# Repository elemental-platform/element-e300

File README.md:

# element-e300
Wireless carbon dioxide sensor based on RFM69 radio

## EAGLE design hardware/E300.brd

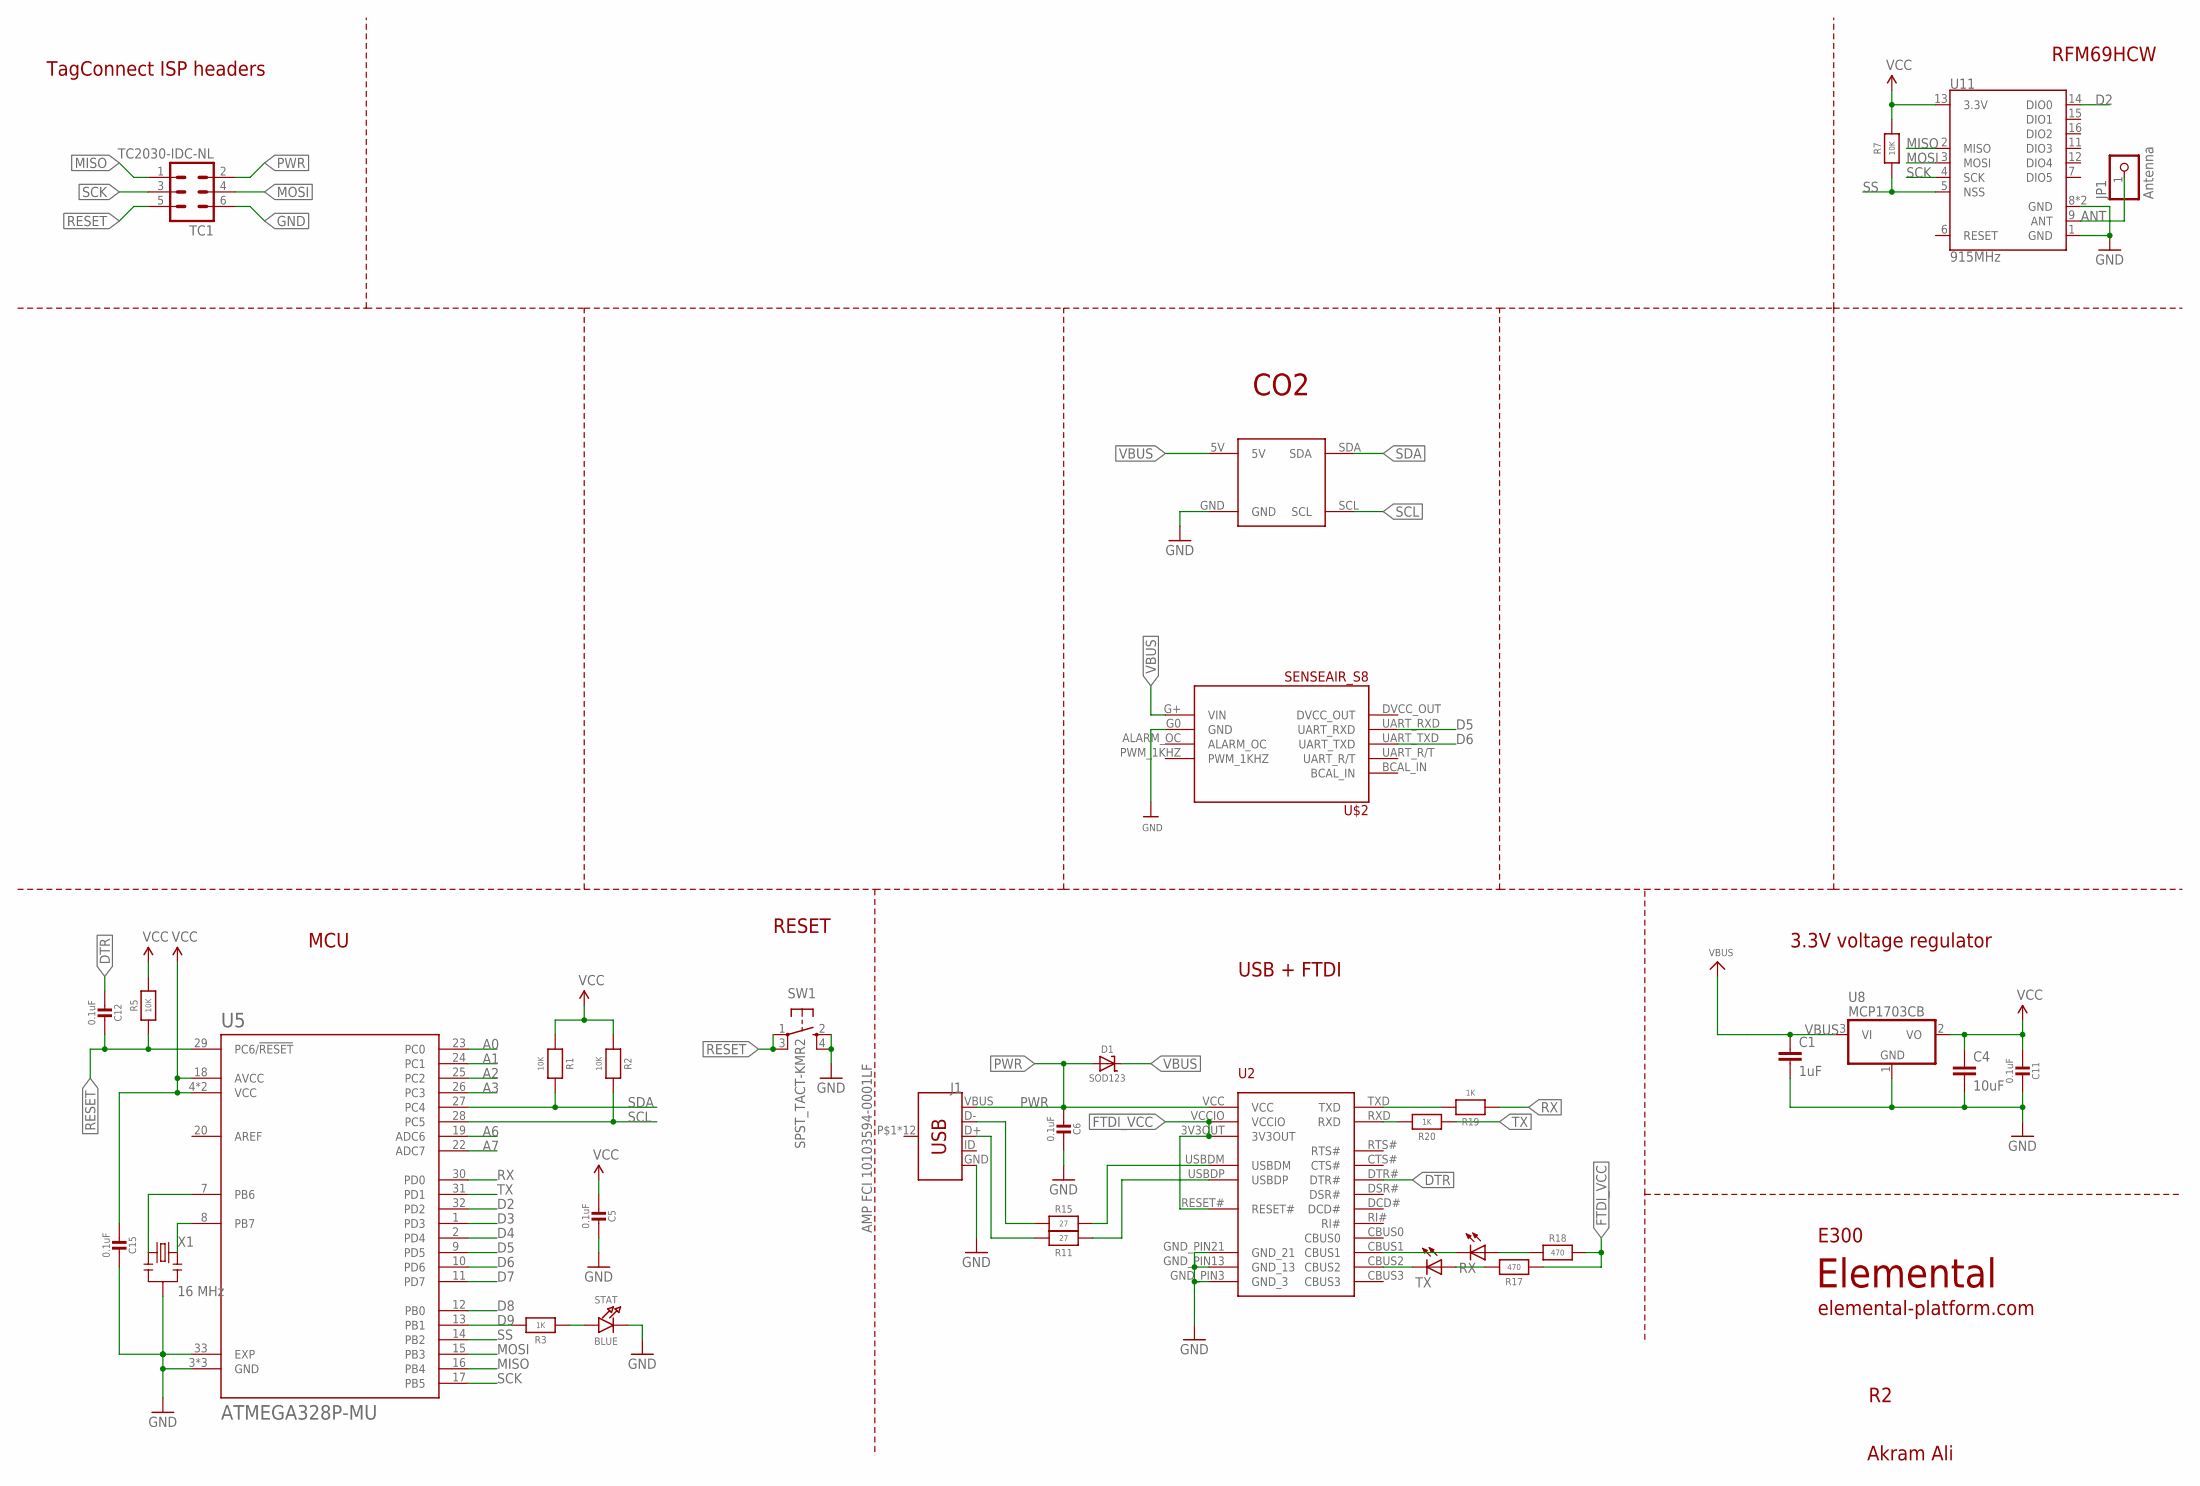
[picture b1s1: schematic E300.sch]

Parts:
C1: 1uF; 0805; MPN CC0805ZRY5V8BB105
C4: 10uF; 0805; MPN CC0805KKX5R6BB106
C5, C6, C11, C12, C15: 0.1uF; MICROBUILDER__0402MP; MPN GRM155R71C104KA88J
D1: SOD123; MICROBUILDER_SOD-123; MPN SD103AW-13-F
J1: AMP FCI 10103594-0001LF; USB-MICROB-PTH
JP1: Antenna; 1X01-CLEANBIG; MPN Helical antenna
R1, R2: 10K; MICROBUILDER__0402MP; MPN RC0402JR-071KL
R3: 1K; MICROBUILDER__0402MP; MPN RC0402JR-0710KL
R5, R7: 10K; MICROBUILDER__0402MP; MPN RC0402JR-0710KL
R11, R15: 27; MICROBUILDER__0402MP; MPN RC0402JR-0727RL
R17, R18: 470; MICROBUILDER__0402MP; MPN RC0402JR-07470RL
R19, R20: 1K; MICROBUILDER__0402MP; MPN RC0402JR-071KL
RX: LEDCHIPLED_0805; CHIPLED_0805; MPN LG R971-KN-1
STAT: BLUE; CHIPLED_0805_NOOUTLINE
SW1: SPST_TACT-KMR2; KMR2
TC1: TC2030-IDC-NL
TX: LEDCHIPLED_0805; CHIPLED_0805; MPN LG R971-KN-1
U2: FT231XQ-R; FTDI_FT231XQ-R_PACKAGE; MPN FT231XQ-R
U5: ATMEGA328P-MU; QFN50P500X500X100-33N; MPN ATMEGA328P-MU
U6: K30-CO2-I2C
U8: MCP1703CB; SOT23; MPN MCP1703T-3302E/CB
U11: 915MHz; RFM69HCW-XXXS2; MPN RFM69HCW
U$2: SENSEAIR_S8
X1: 16 MHz; RESONATOR-SMD; MPN CSTCE16M0V53-R0

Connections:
A0: U5.23 (PC0)
A1: U5.24 (PC1)
A2: U5.25 (PC2)
A3: U5.26 (PC3)
A6: U5.19 (ADC6)
A7: U5.22 (ADC7)
ANT: JP1.1, U11.9 (ANT)
D2: U5.32 (PD2), U11.14 (DIO0)
D3: U5.1 (PD3)
D4: U5.2 (PD4)
D5: U5.9 (PD5), U$2.UART_RXD
D6: U5.10 (PD6), U$2.UART_TXD
D7: U5.11 (PD7)
D8: U5.12 (PB0)
D9: R3.2, U5.13 (PB1)
DTR: C12.2, U2.DTR#
FTDI_VCC: R17.1, R18.2, U2.3V3OUT, U2.RESET#, U2.VCCIO
GND: C1.2, C4.2, C5.1, C6.1, C11.1, C15.1, J1.GND, STAT.C, SW1.2 (S), SW1.4 (S1), TC1.6, U2.GND_PIN3 (GND_3), U2.GND_PIN13 (GND_13), U2.GND_PIN21 (GND_21), U5.3 (GND), U5.5 (GND), U5.21 (GND), U5.33 (EXP), U6.GND, U8.1 (GND), U11.1 (GND), U11.8 (GND), U11.10 (GND), U$2.G0 (GND), X1.2
MISO: TC1.1, U5.16 (PB4), U11.2 (MISO)
MOSI: TC1.4, U5.15 (PB3), U11.3 (MOSI)
unnamed: R20.2, U2.RXD
unnamed: R19.2, U2.TXD
unnamed: U5.8 (PB7), X1.3
unnamed: U5.7 (PB6), X1.1
unnamed: R3.1, STAT.A
unnamed: RX.C, U2.CBUS1
unnamed: TX.C, U2.CBUS2
unnamed: R15.2, U2.USBDM
unnamed: R11.1, U2.USBDP
unnamed: R18.1, RX.A
unnamed: R17.2, TX.A
unnamed: J1.D-, R15.1
unnamed: J1.D+, R11.2
PWR: C6.2, D1.A, J1.VBUS, TC1.2, U2.VCC
RESET: C12.1, R5.1, SW1.1, SW1.3 (P1), TC1.5, U5.29 (PC6/!RESET)
RX: R19.1, U5.30 (PD0)
SCK: TC1.3, U5.17 (PB5), U11.4 (SCK)
SCL: R2.2, U5.28 (PC5), U6.SCL
SDA: R1.2, U5.27 (PC4), U6.SDA
SS: R7.1, U5.14 (PB2), U11.5 (NSS)
TX: R20.1, U5.31 (PD1)
VBUS: C1.1, D1.C, U6.5V, U8.3 (VI), U$2.G+ (VIN)
VCC: C4.1, C5.2, C11.2, C15.2, R1.1, R2.1, R5.2, R7.2, U5.4 (VCC), U5.6 (VCC), U5.18 (AVCC), U8.2 (VO), U11.13 (3.3V)

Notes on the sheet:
TagConnect ISP headers
3.3V voltage regulator
Elemental
E300
Akram Ali
USB + FTDI
elemental-platform.com
RFM69HCW
MCU
RESET
CO2

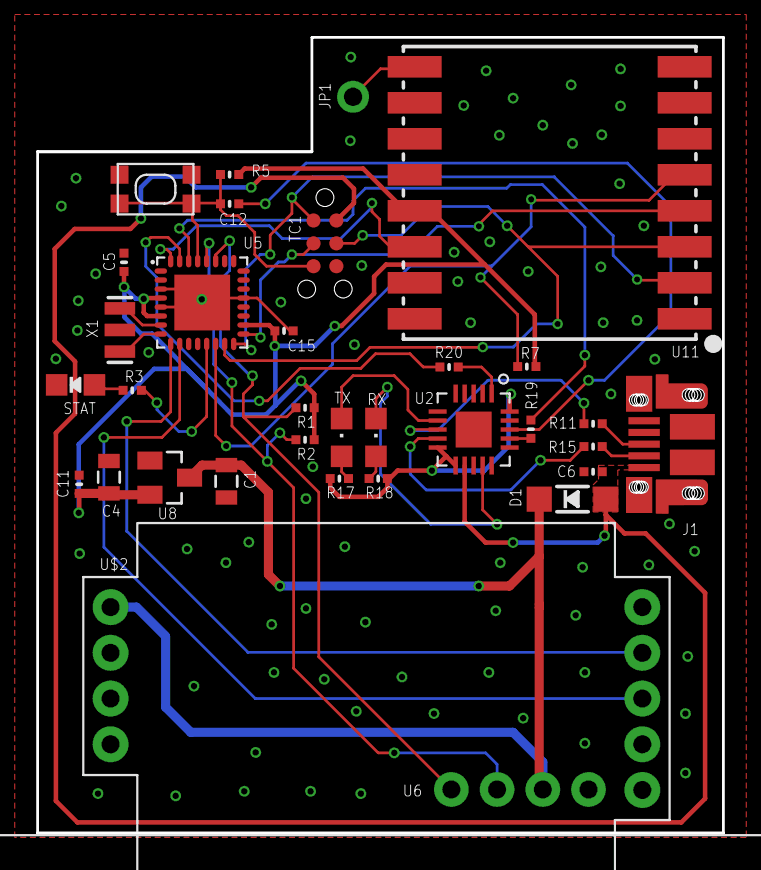
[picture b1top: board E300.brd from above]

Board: 2 copper layers, 38.1 x 44.2 mm, 33 parts (0 on the bottom side), 33 nets.

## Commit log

2019-09-02 Create LICENSE
2019-12-23 Update firmware.ino
    removed node ID from datapacket (gateway already has it in the encrypted packet, so it can retrieve it directly)
2020-01-29 Update firmware.ino
    freq change and encryption key change
2020-02-05 cleaned up
    - added control node check
    - minimized some delays

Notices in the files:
parts and their libraries:
SparkFun-Connectors: Licensing: Creative Commons ShareAlike 4.0 International - https://creativecommons.org/licenses/by-sa/4.0
microbuilder: This work is placed in the public domain, and may be freely used for commercial and non-commercial work with the following conditions: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
